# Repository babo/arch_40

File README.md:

## Arch 40

#### Case Renders:

#### Switch Plate:

## 40% Ortholinear + Columnar Stagger Keyboard
* Inspired by the Ergodox, Atreus, Iris, Corne, and probably others

* Design goals:
    * Efficiency and minimalism of a 40% form factor
    * Ergo benefits of tilted columnar stagger layout
    * Ease of use coming from ANSI style layouts
    * Simplicity of a non-split keyboard
    * Compatability with Ergodox style keysets
    * Compatible with Cherry MX, Alps, and Kailh Choc switches

----

## Assembly:
* Stacked acrylic layer case, acrylic/metal switch plate 
    * Layer dimensions and path lengths are outlined in `path_length.md`
    * Alternatively, there is a 2-part case in `./cad_files/stl_files/3d_print_case` designed to be 3D printed and fastened together with machine screws
* Can be built with a PCB and microcontroller, or can be handwired with a microcontroller
* Files for laser cutting by Ponoko/other services in `./illustrator_files` and `./inkscape_files`
    * `./illustrator_files` includes case layer DXF files imported into Adobe Illustrator at 1:1 scale with units in millimeters
        * `final_cut_layout.eps` is Ponoko's P3 size template with case layers, **without plate**
            * Use this if you choose to go with a metal plate
        * `final_cut_layout_plate.eps` is Ponoko's P3 size template with case layers, **with plate**
            * Use this if you choose to go with an acrylic plate

    * `./inkscape_files` includes pdf-compatible Adobe `.ai` files as well as `.SVG` files of the case layers and plate
____

#### Component list:
* Acrylic case layers + plate
* PCB (optional, can be handwired as well)
    * Pro Micro (PCB is designed to use this microcontroller)
    * Teensy2.0 (if handwiring and not using PCB)
* (49) Cherry MX style switches
* (1) 2u Cherry style stabilizer
    * **Plate-mounted** works perfectly with 1.5mm metal switch plate
    * **Requires some modification** to work properly with 3.0mm acrylic plate
* Adafruit USB-mini breakout board (or a simple female USB-mini)
* WS2812B LED strips (optional)
* (49) 1N4184 diodes
* M2 Standoffs and screws
    * 5mm screw length
    * 10mm standoff length for use with a **1.5mm metal plate**
    * 12mm standoff length for use with a **3.0mm acrylic plate**

____

#### Case Stack Order:
1) `arch_40_case_layer0`
2) `arch_40_plate`
3) `arch_40_case_layer2-3`
4) `arch_40_case_layer2-3` (repeated)
5) `arch_40_case_layer4`
7) `arch_40_case_layer5`

* **Note:** `arch_40_case_layer2-3` is intended to be used twice, it contains the cutout for the USB connection

____

#### PCB:
##### Revision history:
* rev 0: prototype, designed by [ibnuda](https://github.com/ibnuda)
* rev 1: better case fitment, functionally same as rev 0
* rev 1.1: added support for MX, Alps, Kailh Choc switches

----

* QMK files for PCB firmware in `./firmware/qmk_files`
* PCB can be made by sending the zipped gerber files in `./pcb/gerbers/arch_40_rev1.1_gerber.zip` to a PCB prototyping service such as [JLCPCB](https://jlcpcb.com)
* **Note**: The Pro Micro controller needs to be soldered onto the PCB as close as possible, need to remove the spacers on the headers of the Pro Micro

----

##### Pro Micro Pinout:
* Diode direction: row to column
* Column 0 = ESC key column
* Row 0 = QWERTY row
~~~
Rows:              Columns:                            LED:
-----------------------------------------------------------------
r0 : D3            c0 : F4         c6 : B2             vcc : VCC
r1 : D1            c1 : F5         c7 : B6             gnd : GND
r2 : D0            c2 : F6         c8 : B5            data : D2
r3 : D4            c3 : F7         c9 : B4
                   c4 : B1        c10 : E6
                   c5 : B3        c11 : D7
                                  c12 : C6
~~~
____

#### Handwiring:

##### Matrix:

##### Teensy2.0 Pinout:
* Diode direction: column to row
* Column 0 = ESC key column
* Row 0 = QWERTY row
~~~
Rows:               Columns:                            LED:
-----------------------------------------------------------------
r0 : F0             c0 : F7         c6 : C6             vcc : VCC
r1 : F1             c1 : B6         c7 : D3             gnd : GND
r2 : F4             c2 : B5         c8 : D2            data : B1 
r3 : F5             c3 : B4         c9 : D1
r4 : F6             c4 : D7        c10 : D0
                    c5 : C7        c11 : B7
~~~

##### Wiring Example:

##### Wiring Example With Underglow LED's:

## Firmware Flashing:

#### PCB Builds:
##### Linux:
* The Pro Micro controller can be flashed with [avrdude](https://www.nongnu.org/avrdude/)

    * Navigate to the `./firmware` directory to flash the `arch40firmware_pcb.hex` file:

    `$ avrdude -p atmega32u4 -P /dev/ttyACM0 -c avr109 flash:w:arch40firmware_pcb.hex`

    * Or to the `./firmware/qmk_files` to flash the `arch40_promicro_default.hex` file

    `$ avrdude -p atmega32u4 -P /dev/ttyACM0 -c avr109 flash:w:arch40_promicro_default.hex`

* They are the same keymap, the former was created with Keyboard Firmware Builder, and the latter with QMK

##### Windows/MacOS:
* Can be done using [QMK Toolbox](https://github.com/qmk/qmk_toolbox)

##### LED Backlighting:
* Default firmware `arch40firmware_pcb.hex` and `arch40_promicro_default.hex` includes configuration for WS2812B LED backlighting strips
    * The data pin for the LED's is set to pin D2 on the Pro Micro
    * Default 12 LED quantity, 10 backlight brightness levels, variable color hue
    * To change the LED configuration:
        1) The `arch40firmware_pcb.json` file can be uploaded to [Keyboard Firmware Builder](https://kbfirmware.com/) and edited/recompiled as desired
        2) The QMK source files can be edited manually in a text editor
____

#### Handwired Builds:
* Linux:
    * The Teensy2.0 controller can be flashed with the [teensy-loader-cli](https://www.pjrc.com/teensy/loader_cli.html)

~~~
$ teensy-loader-cli --mcu=atmega32u4 -w -v ./firmware/arch40firmware_hw.hex
~~~
* MacOS/Windows:
    * Can be flashed with the [Teensy Loader Application](https://www.pjrc.com/teensy/loader.html)
    * Or can be done using [QMK Toolbox](https://github.com/qmk/qmk_toolbox)
##### LED Backlighting:
* Default firmware `arch40firmware_hw.hex` includes configuration for WS2812B LED backlighting strips
    * The data pin for the LED's is set to pin B1 on the Teensy2.0

## Note:
* Kerf of plate and case layers is set to 0.15mm (typical for Ponoko/ Laserboost/ Lasergist)

## To-do:
* Add image of default keymap

###### Model was created in Solidworks, then exported as STL/DXF. Feel free to use/modify/redistribute.

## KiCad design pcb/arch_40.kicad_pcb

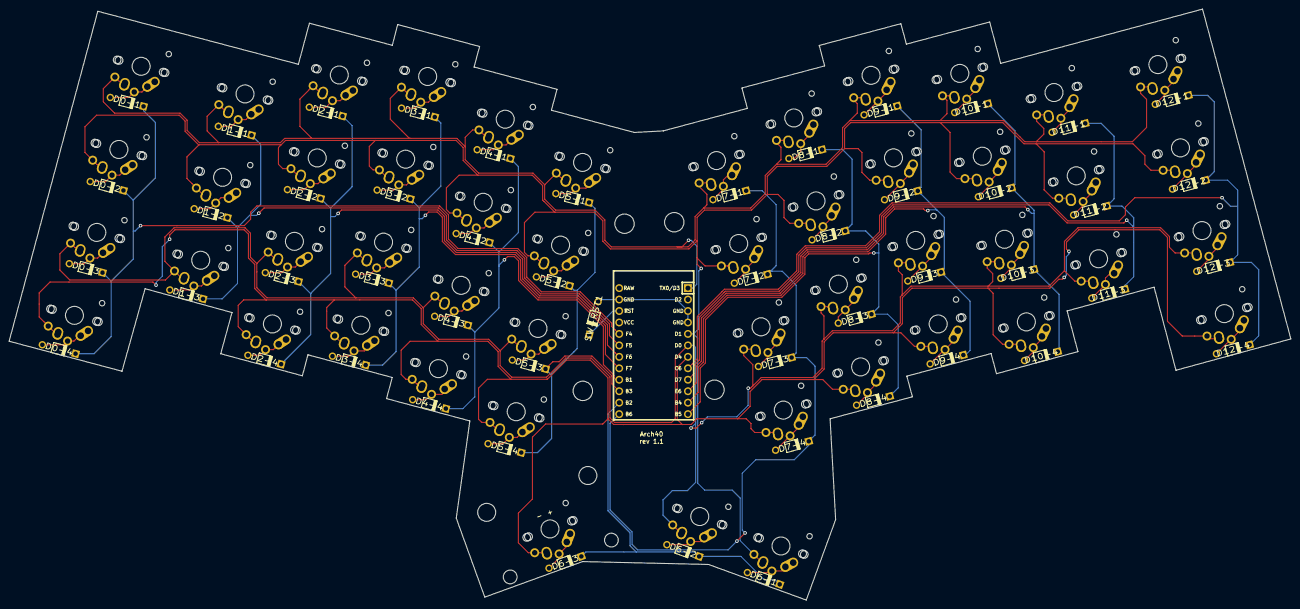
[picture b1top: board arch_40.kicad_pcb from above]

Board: 2 copper layers, 284.2 x 131.0 mm, 100 parts (1 on the bottom side), 68 nets.

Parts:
D0-1, D0-2, D0-3, D0-4, D1-1, D1-2, D1-3, D2-1, D2-2, D2-3, D2-4, D3-1, D3-2, D3-3, D3-4, D4-1, D4-2, D4-3, D4-4, D5-1, D5-2, D5-3, D5-4, D6-1, D6-2, D6-3, D7-1, D7-2, D7-3, D7-4, D8-1, D8-2, D8-3, D8-4, D9-1, D9-2, D9-3, D9-4, D10-1, D10-2, D10-3, D10-4, D11-1, D11-2, D11-3, D12-1, D12-2, D12-3, D12-4: DIODE; Diode
SW0-1, SW0-2, SW0-3, SW0-4, SW1-1, SW1-2, SW1-3, SW2-1, SW2-2, SW2-3, SW2-4, SW3-1, SW3-2, SW3-3, SW3-4, SW4-1, SW4-2, SW4-3, SW4-4, SW5-1, SW5-2, SW5-3, SW5-4, SW6-1, SW6-2, SW7-1, SW7-2, SW7-3, SW7-4, SW8-1, SW8-2, SW8-3, SW8-4, SW9-1, SW9-2, SW9-3, SW9-4, SW10-1, SW10-2, SW10-3, SW10-4, SW11-1, SW11-2, SW11-3, SW12-1, SW12-2, SW12-3, SW12-4: SWITCH_PUSH; MX-Alps-Choc-1U-NoLED
SW6-3: SWITCH_PUSH; MX-Alps-Choc-2U-StabNormal-noled-alt
SW-RST1: SWITCH_PUSH; Diode
U1: ARDUINO_PRO_MICRO; ArduinoProMicro

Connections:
/COL0: D0-1.2, D0-2.2, D0-3.2, D0-4.2, U1.20
/COL1: D1-1.2, D1-2.2, D1-3.2, U1.19
/COL2: D2-1.2, D2-2.2, D2-3.2, D2-4.2, U1.18
/COL3: D3-1.2, D3-2.2, D3-3.2, D3-4.2, U1.17
/COL4: D4-1.2, D4-2.2, D4-3.2, D4-4.2, U1.16
/COL5: D5-1.2, D5-2.2, D5-3.2, D5-4.2, U1.15
/COL6: D6-1.2, D6-2.2, D6-3.2, U1.14
/COL7: D7-1.2, D7-2.2, D7-3.2, D7-4.2, U1.13
/COL8: D8-1.2, D8-2.2, D8-3.2, D8-4.2, U1.12
/COL9: D9-1.2, D9-2.2, D9-3.2, D9-4.2, U1.11
/COL10: D10-1.2, D10-2.2, D10-3.2, D10-4.2, U1.10
/COL11: D11-1.2, D11-2.2, D11-3.2, U1.9
/COL12: D12-1.2, D12-2.2, D12-3.2, D12-4.2, U1.8
/ROW-1: SW0-1.1, SW1-1.1, SW2-1.1, SW3-1.1, SW4-1.1, SW5-1.1, SW7-1.1, SW8-1.1, SW9-1.1, SW10-1.1, SW11-1.1, SW12-1.1, U1.1
/ROW-2: SW0-2.1, SW1-2.1, SW2-2.1, SW3-2.1, SW4-2.1, SW5-2.1, SW6-1.1, SW7-2.1, SW8-2.1, SW9-2.1, SW10-2.1, SW11-2.1, SW12-2.1, U1.5
/ROW-3: SW0-3.1, SW1-3.1, SW2-3.1, SW3-3.1, SW4-3.1, SW5-3.1, SW6-2.1, SW7-3.1, SW8-3.1, SW9-3.1, SW10-3.1, SW11-3.1, SW12-3.1, U1.6
/ROW-4: SW0-4.1, SW2-4.1, SW3-4.1, SW4-4.1, SW5-4.1, SW6-3.1, SW7-4.1, SW8-4.1, SW9-4.1, SW10-4.1, SW12-4.1, U1.7
GND: SW-RST1.1, U1.3, U1.4, U1.23
unnamed: D0-1.1, SW0-1.2
unnamed: D0-2.1, SW0-2.2
unnamed: D0-3.1, SW0-3.2
unnamed: D0-4.1, SW0-4.2
unnamed: D1-1.1, SW1-1.2
unnamed: D1-2.1, SW1-2.2
unnamed: D1-3.1, SW1-3.2
unnamed: D2-1.1, SW2-1.2
unnamed: D2-2.1, SW2-2.2
unnamed: D2-3.1, SW2-3.2
unnamed: D2-4.1, SW2-4.2
unnamed: D3-1.1, SW3-1.2
unnamed: D3-2.1, SW3-2.2
unnamed: D3-3.1, SW3-3.2
unnamed: D3-4.1, SW3-4.2
unnamed: D4-1.1, SW4-1.2
unnamed: D4-2.1, SW4-2.2
unnamed: D4-3.1, SW4-3.2
unnamed: D4-4.1, SW4-4.2
unnamed: D5-1.1, SW5-1.2
unnamed: D5-2.1, SW5-2.2
unnamed: D5-3.1, SW5-3.2
unnamed: D5-4.1, SW5-4.2
unnamed: D6-1.1, SW6-1.2
unnamed: D6-2.1, SW6-2.2
unnamed: D6-3.1, SW6-3.2
unnamed: D7-1.1, SW7-1.2
unnamed: D7-2.1, SW7-2.2
unnamed: D7-3.1, SW7-3.2
unnamed: D7-4.1, SW7-4.2
unnamed: D8-1.1, SW8-1.2
unnamed: D8-2.1, SW8-2.2
unnamed: D8-3.1, SW8-3.2
unnamed: D8-4.1, SW8-4.2
unnamed: D9-1.1, SW9-1.2
unnamed: D9-2.1, SW9-2.2
unnamed: D9-3.1, SW9-3.2
unnamed: D9-4.1, SW9-4.2
unnamed: D10-1.1, SW10-1.2
unnamed: D10-2.1, SW10-2.2
unnamed: D10-3.1, SW10-3.2
unnamed: D10-4.1, SW10-4.2
unnamed: D11-1.1, SW11-1.2
unnamed: D11-2.1, SW11-2.2
unnamed: D11-3.1, SW11-3.2
unnamed: D12-1.1, SW12-1.2
unnamed: D12-2.1, SW12-2.2
unnamed: D12-3.1, SW12-3.2
unnamed: D12-4.1, SW12-4.2
unnamed: SW-RST1.2, U1.22

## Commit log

2019-11-13 fixed cutout.
2019-11-13 renamed handwired firmware files
2019-11-13 added license
2019-11-13 fixed .ai files stroke width
2019-11-14 added zipped gerber files
2019-11-19 added pcb firmware
2019-11-20 added inkscape compat files
2019-11-21 updated pcb rev1
2019-11-22 updated pcb firmware
2019-11-22 updated case filenames
2019-11-23 revert case layer filenames
2019-12-03 updated qmk files
2019-12-04 updated qmk keymap.c
2019-12-04 updated qmk json
2019-12-13 added STL files for 3d printing
2019-12-14 updated qmk info.json
2019-12-14 updated qmk readme
2019-12-25 updated pcb rev1.1
2020-03-20 Add zen theme
2020-03-20 Add sample site
2020-03-20 Add generated site
2020-03-20 Add absolet path
2020-03-20 fix path
2020-03-20 remove draft
2020-03-20 Fix image
2020-03-20 Use relative url
2020-03-20 set base url as /
2020-03-20 use absolute url
2020-03-20 Use a bundle
2020-03-20 Add theme config
